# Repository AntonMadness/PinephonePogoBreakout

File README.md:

# PinephonePogoBreakout

Fork from: SMR404/PinephonePogoBreakout

This edition is made so, it only uses single sided PCB. As well as an easier shape to cut for home fabrication.

A breakout board for the Pinephone's expansion port, which consists of 6 pogo pins connected to I2C (SDA and SCL), the battery (at 3.8V), a 5V (supplied only and directly from USB), an interrupt pin, and GND.

Also the standoff/washer .stl file is for 3d printing; it's used because I left the three holes in the pcb larger than necessary to allow some wiggle room, and the machine screw (which is M1.4 by the way) will slip through it otherwise.

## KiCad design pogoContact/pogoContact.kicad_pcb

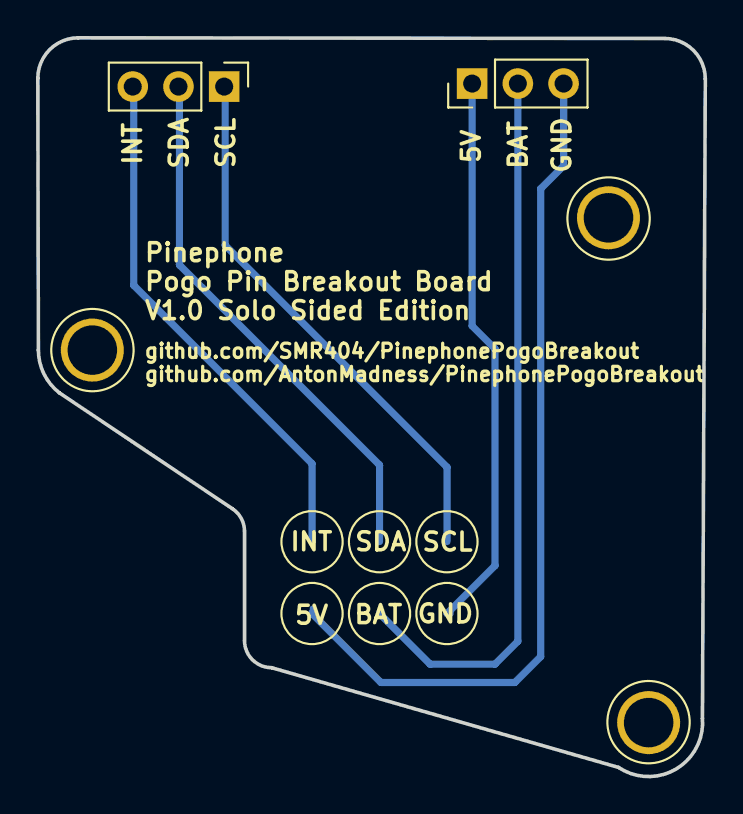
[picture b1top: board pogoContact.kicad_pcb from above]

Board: 2 copper layers, 37.1 x 41.0 mm, 3 parts (1 on the bottom side), 6 nets.

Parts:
J1: Conn_01x06; PP_6_pogo_pin_contacts
J2, J3: Conn_01x03; PinHeader_1x03_P2.54mm_Vertical

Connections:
unnamed: J1.1, J2.1
unnamed: J1.2, J2.2
unnamed: J1.3, J2.3
unnamed: J1.4, J3.1
unnamed: J1.5, J3.2
unnamed: J1.6, J3.3

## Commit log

2020-12-24 Update README.md
    Information on pins, power and voltages now available on wiki, on the blog of Martijn (https://blog.brixit.nl/making-a-backcover-extension-for-the-pinephone/) and also tested it myselfs.
2020-12-24 Add files via upload
    trying this update thing?
2020-12-24 Add files via upload
    simplyfied the board to a single side design and easier to cut.
